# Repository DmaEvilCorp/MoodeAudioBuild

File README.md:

# MoodeAudioBuild
Just a build report, may help or give idea to other people.
Using a Raspberry Pi 2b+ (512mb ram) with MoodeAudio 6.7.1 on a 32GB MicroSD + AudioPhonics DAC ES9023 V1.
http://moodeaudio.org/

Case Hammond 1455T2202BK (220x165x51.5mm) black aluminium.
Front and back are in plastic, much easier for working.
I've used FrontPanel from Schaeffer to make the design.

Power supply :
- Toroidal transformer 2x115vac / 2x15vac 18VA (modified to 1x15vac / 1x8vac).
- 5vdc regulator with a LD1805 (2x2200uF) (BYV-100 Diode).

Power supply controler :
- Attiny 13A who control 2 relay.
  - First relay control de power to the rpi.
  - Second relay send a short contact to a GPIO witch is configure to shutdown the rpi.
  - 1 button (First push = Power ON / Second long push = Power OFF after 1 min).
- See Kicad schematic & Arduino Code (Using MicroCore https://github.com/MCUdude/MicroCore) & Usbasp for programming.

Display :
- Using a HD44780 compatible display 2x20.
- Drive by pydPiper https://github.com/dhrone/pydPiper.
- pydPiper is running outside of docker for performance (pi2 too slow).
  - Autostart in /etc/rc.local by adding the line (at the end of the file) sudo sh /home/pi/pydpiper.sh &
  - pydpiper.sh simply do :
    - cd /home/pi/pydPiper
    - sudo python pydPiper.py
    
Todo :
- Upgrade to MoodeAudio 7.x.
- Resolve GPIO bug.
- Print front panel to cover the screw.

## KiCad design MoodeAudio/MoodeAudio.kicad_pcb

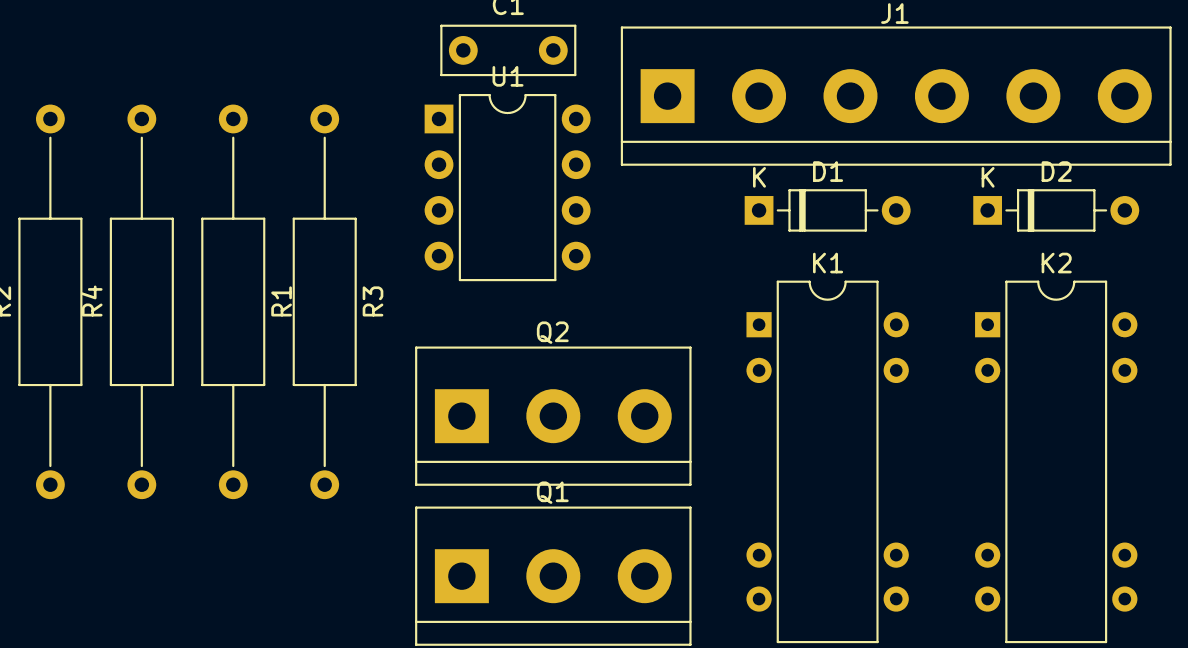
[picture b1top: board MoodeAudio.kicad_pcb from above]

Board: 2 copper layers, 13 parts (0 on the bottom side), 14 nets, no tracks yet.

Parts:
C1: 100nF; C_Rect_L7.2mm_W2.5mm_P5.00mm_FKS2_FKP2_MKS2_MKP2
D1, D2: 1N4148; D_DO-35_SOD27_P7.62mm_Horizontal
J1: Conn_01x06_Female; TerminalBlock_bornier-6_P5.08mm
K1, K2: DIPxx-1Axx-11x; Relay_StandexMeder_DIP_LowProfile
Q1, Q2: Q_NPN_BCE; TerminalBlock_bornier-3_P5.08mm
R1, R2, R3, R4: 10K; R_Axial_DIN0309_L9.0mm_D3.2mm_P20.32mm_Horizontal
U1: ATtiny13-20PU; DIP-8_W7.62mm

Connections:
GND: C1.1, J1.2, Q1.3, Q2.3, U1.4
unnamed: C1.2, D1.1, D2.1, J1.1, K1.6, K1.7, K1.8, K2.6, R1.1, R3.1, U1.8
unnamed: D1.2, K1.2, Q1.2
unnamed: D2.2, K2.2, Q2.2
unnamed: J1.3, R3.2
unnamed: J1.4, U1.7
unnamed: J1.5, K2.7, K2.8
unnamed: J1.6, K2.1, K2.14
unnamed: K1.1, K1.14
unnamed: Q1.1, R2.1
unnamed: Q2.1, R4.1
unnamed: R1.2, U1.1
unnamed: R2.2, U1.6
unnamed: R4.2, U1.5

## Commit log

2021-01-10 Add files via upload
    For HD44780 20x2
